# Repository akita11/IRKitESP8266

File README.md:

IRKitESP8266
=====

IRKit Clone on ESP8266

## これは何

Toshiyuki Kawashima氏の[ESP8266IRKit](https://github.com/toskaw/ESP8266IRKit) をベースに、以下の2点の追加・改変を行ったものです。
* ボタンを追加、長押しで初期化(電源ON時にも有効)
* 動作状態をLED(WS2812B)で表示

## 基板データ

IRKitESP8266.{brd,sch}がEagleデータです。適当な方法で製造してください。

※LED電流制限抵抗としてR4とR11の2つがありますが、どちらか一方のみの実装でよいです。流れる電流からして、R11のほうがオススメです（13Ωと書いてありますが、10Ω前後のものでよいはず）。ただこのあたりは要調整で、SwitchScienceのESP-IRではもっと小さな抵抗を使っているようです。10Ωか4.7Ωの0603サイズ（インチ：ミリだと1608）を、R4とR11の両方に実装するくらいでいいかもです（試していないのでLED破損の恐れがありますので要注意）。

なおオリジナルIRKitの基板と、穴の位置やコネクタの位置を基本的にあわせてあるので、オリジナルの筐体を流用できます。ただしオリジナルの赤外線LEDは2個なので、その筐体に合わせる場合は、LEDはD3とD4のみとりつけ、電流制限抵抗R4/R11もそれにあわせて調節してください。なおステータス表示LEDは基板上に上向きに実装されるため、オリジナル筐体にはあいません。またタクトスイッチの位置・種類がオリジナルと異なります。ご了承ください。

※初期化用タクトスイッチをオリジナル筐体にあうように追加し、プログラム用ショートピンの位置を少しずらし、ESP8266のアンテナ周囲のベタGNDを設計ガイドラインにあわせてあけたv1.1を追加しました(C5の位置が変更になっています)。ただし実際の製造・検証はしてませんのでご了承ください。

## ソースコード

上記のToshiyuki Kawashima氏の「作り方（ソースからコンパイルする方法）」の通りに進めます。

## 使い方

基本的に純正IRKitと同じです。スマホのIRKitアプリで初期設定を行ってください。初期パスワードは"0000000000"です。

## 参考にしたもの

* [minlRum](https://github.com/9SQ/minIRum)

* [IRKit](http://getirkit.com/)

* [ESP8266IRKit](https://github.com/toskaw/ESP8266IRKit)

## 直近のToDo
* LED点滅を、一応実装した（1秒周期）が、IR受信時の点滅を本家にあわせたい。
* 基板の外形・部品位置を、オリジナル筐体にあうように、以下の修正をしたい。
** uUSBコネクタの位置
** 初期化タクトスイッチ
** 角を丸める

## Author

Junichi Akita (@akita11, akita@ifdl.jp)

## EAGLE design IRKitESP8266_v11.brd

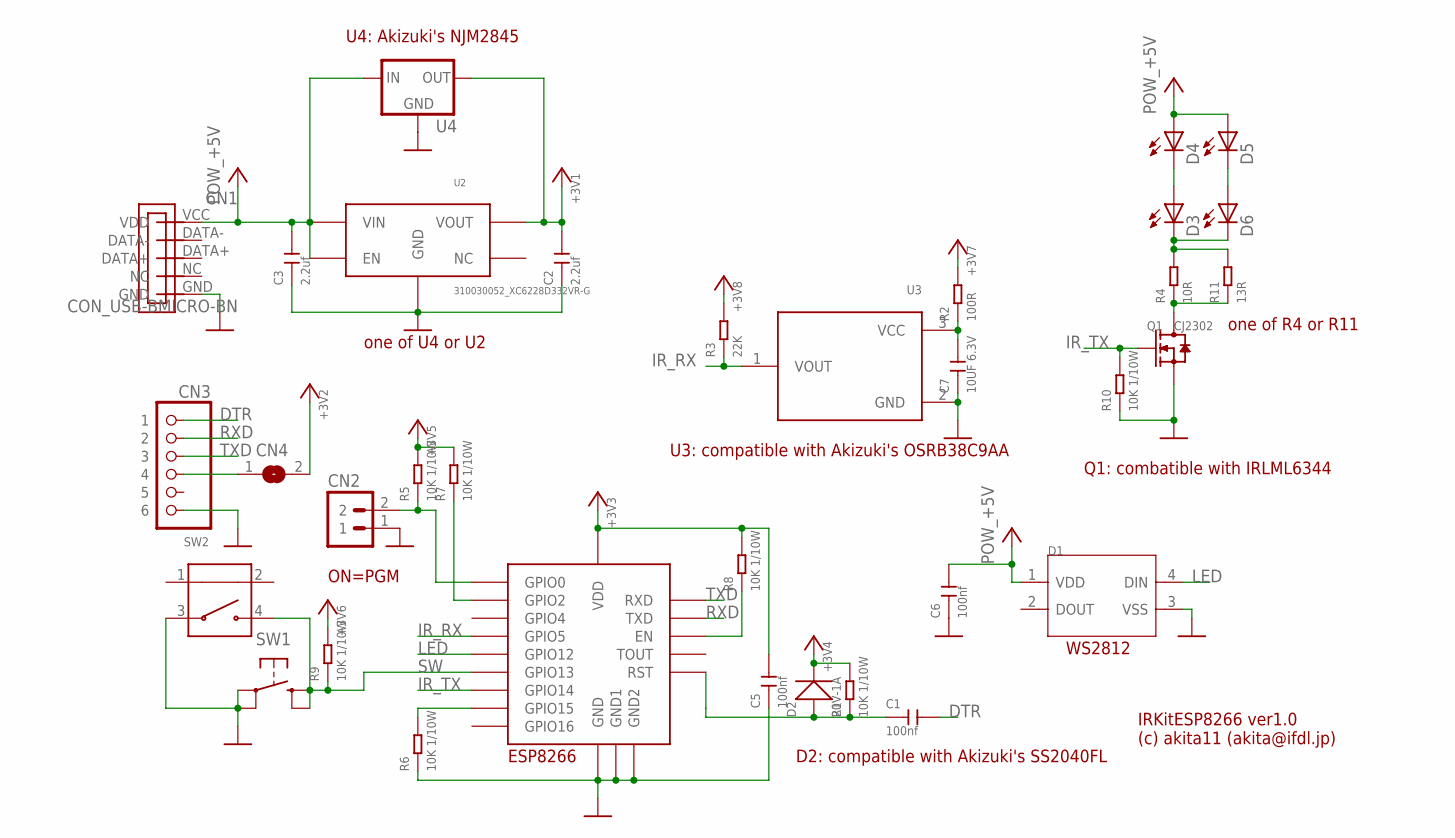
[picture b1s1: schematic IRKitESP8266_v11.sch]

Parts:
C1, C5, C6: 100nf; C0603
C2, C3: 2.2uf; C0603
C7: 10UF 6.3V; C0603
CN1: CON_USB-BMICRO-BN; MICRO-USB_B_NARROW
CN2: CON_PINHD-1X2PTH; SPARKFUN_1X02
CN3: CON_PINHD-1X6; 1X06
CN4: JUMPER_SJ
D1: SMD-RGB-LED-4P'WS2812B'; LED4-SMD-5050
D2: 20V-1A; SOD-123
D3, D4, D5, D6: LED5MM; SPARKFUN_LED5MM
Q1: CJ2302; SOT-23
R1, R5, R6, R7, R8, R9, R10: 10K 1/10W; R0603
R2: 100R; R0603
R3: 22K; R0603
R4: 10R; R0603
R11: 13R; R1206
SW1: SW_TACTTH; SW_B3F-10XX
SW2: TS-1188E
U1: MOD_ESP8266WROOM02
U2: 310030052_XC6228D332VR-G; SOT25J
U3: TSOP382
U4: REG_78XXTO252-3; TO-252-3

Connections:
+3V3: C2.2, C5.2, CN4.2, D2.-, R1.2, R2.2, R3.2, R5.2, R7.2, R8.2, R9.2, U1.P$1 (VDD), U2.P$5 (VOUT), U4.P$3 (OUT)
+5V: C3.2, C6.2, CN1.VCC (VDD), D1.1 (VDD), D4.A, D5.A, U2.P$1 (VIN), U2.P$3 (EN), U4.P$1 (IN)
DTR: C1.2, CN3.1
GND: C2.1, C3.1, C5.1, C6.1, C7.1, CN1.GND, CN2.1, CN3.6, D1.3 (VSS), Q1.2 (S), R6.1, R10.1, SW1.3, SW1.4 (P1), SW2.3, U1.P$9 (GND), U1.P$13 (GND1), U1.P$18 (GND2), U2.P$2 (GND), U3.2 (GND), U4.P$2 (GND)
IR_RX: R3.1, U1.P$14 (GPIO5), U3.1 (VOUT)
IR_TX: Q1.1 (G), R10.2, U1.P$3 (GPIO14)
LED: D1.4 (DIN), U1.P$4 (GPIO12)
unnamed: C1.1, D2.+, R1.1, U1.P$15 (RST)
unnamed: R6.2, U1.P$6 (GPIO15)
unnamed: CN2.2, R5.1, U1.P$8 (GPIO0)
unnamed: R7.1, U1.P$7 (GPIO2)
unnamed: CN3.4, CN4.1
unnamed: R8.1, U1.P$2 (EN)
unnamed: C7.2, R2.1, U3.3 (VCC)
unnamed: Q1.3 (D), R4.1, R11.1
unnamed: D3.K (C), D6.K (C), R4.2, R11.2
unnamed: D3.A, D4.K (C)
unnamed: D5.K (C), D6.A
RXD: CN3.2, U1.P$12 (TXD)
SW: R9.1, SW1.1 (S), SW1.2 (S1), SW2.4, U1.P$5 (GPIO13)
TXD: CN3.3, U1.P$11 (RXD)

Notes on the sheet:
U3: compatible with Akizuki's OSRB38C9AA
D2: compatible with Akizuki's SS2040FL
ON=PGM
WS2812
ESP8266
Q1: combatible with IRLML6344
IRKitESP8266 ver1.0 (c) akita11 (akita@ifdl.jp)
U4: Akizuki's NJM2845
one of U4 or U2
one of R4 or R11

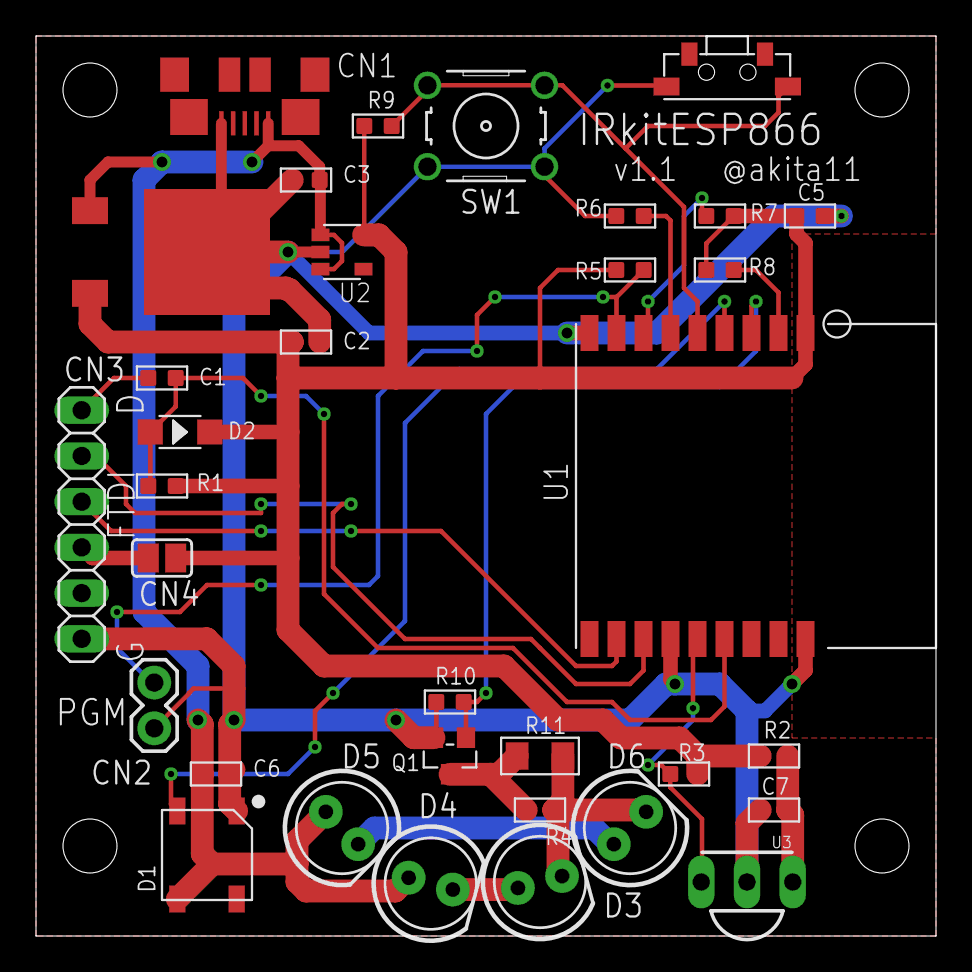
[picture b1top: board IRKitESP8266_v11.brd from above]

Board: 2 copper layers, 50.0 x 50.0 mm, 34 parts (0 on the bottom side), 21 nets.

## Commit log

2018-01-21 必要ファイル一式を追加
2018-01-21 README.mdのプログラム名のtypoを修正
2018-01-22 README.mdのtypoを修正
2018-01-22 README.mdに、LED点滅の実装予定を追記
2018-01-22 README.mdに、抵抗の実装方法について追記
2018-01-22 typoの修正、LED電流制限抵抗に関して追記。
2018-01-22 筐体に関する記述を追加
2018-01-23 初期化用タクトスイッチ（本家と同じ位置）を追加sita
2018-01-23 ESP8266のアンテナ周囲のベタGNDの変更
    設計ガイドに沿って、アンテナ周囲のベタGNDをあけ、それにともなってC5の位置を移動
2018-01-24 ステータスLED点滅の実装
2018-01-30 電源ON時の初期化処理を追加。LED点滅周期・輝度の変更。
    READMEに、オリジナル筐体にあわせるための基板修正案を追記
2018-01-31 ソースの更新忘れを更新
2020-09-15 サーバ問い合わせ間隔を本家IRkitにあわせて5秒ごとに
2020-09-15 サーバ問い合わせ間隔を5秒にするdelayを削除
    そこに入れると赤外線読み取りが止まってしまうため、いったん元に戻す。
